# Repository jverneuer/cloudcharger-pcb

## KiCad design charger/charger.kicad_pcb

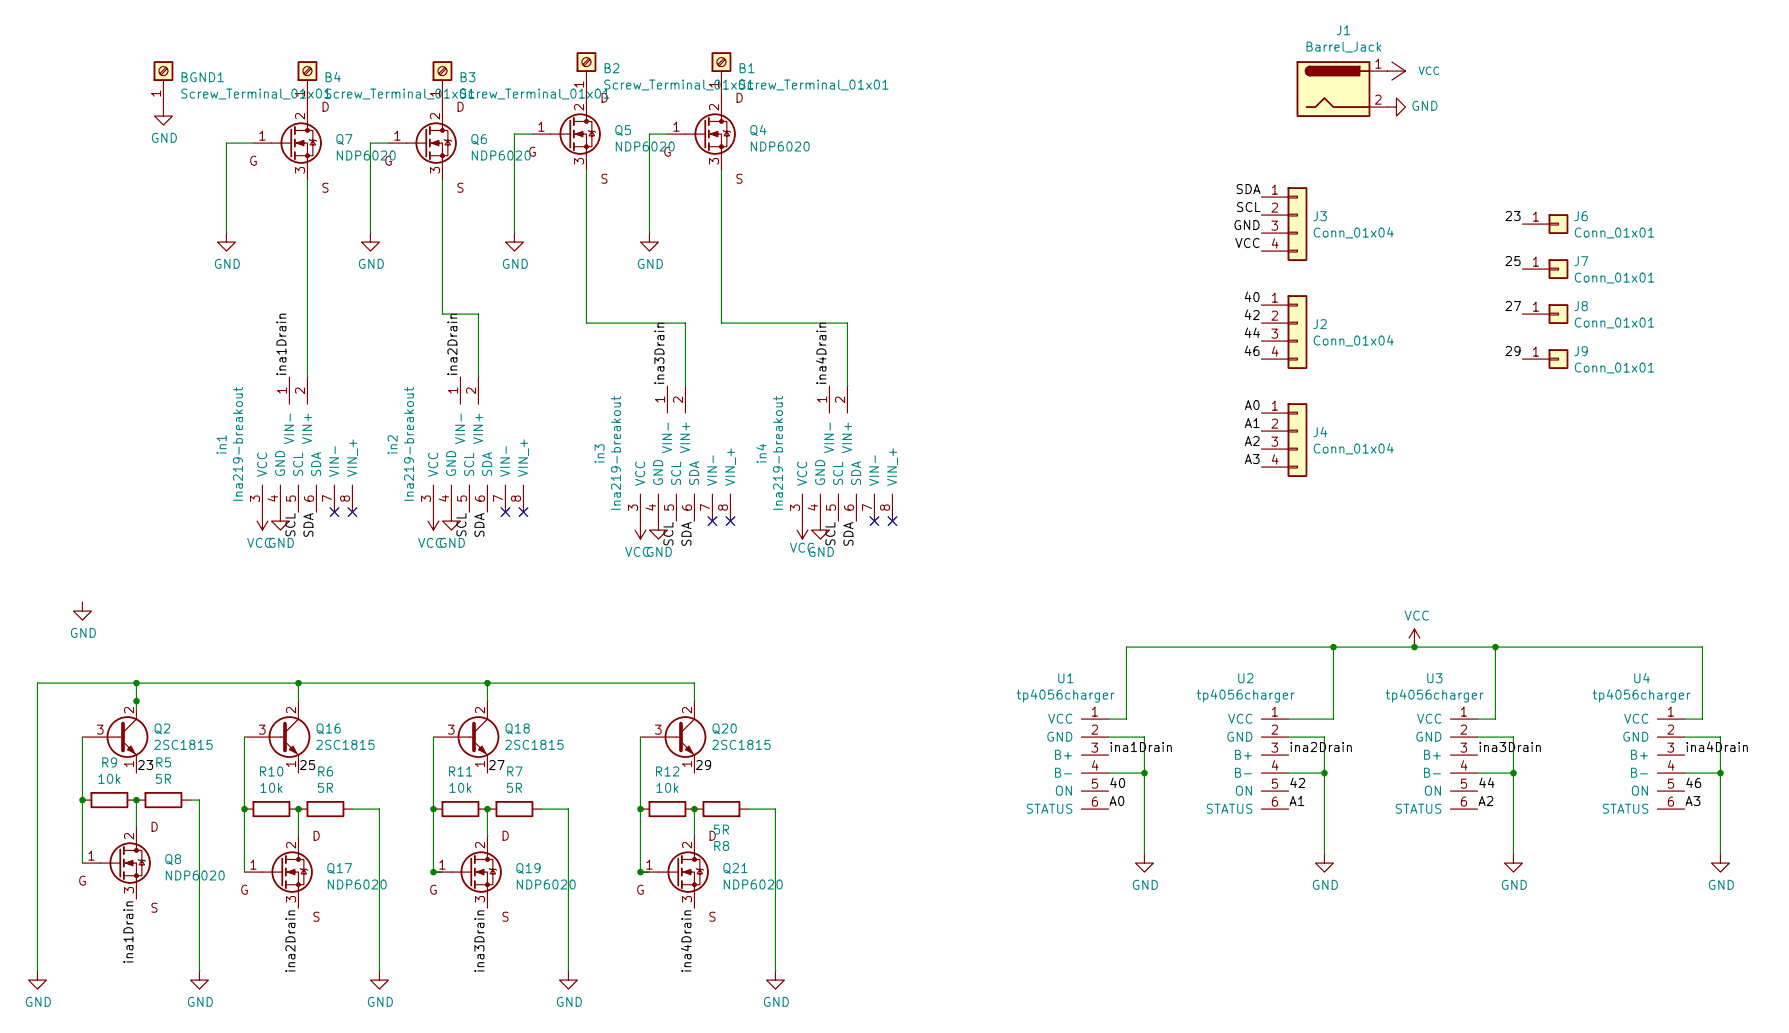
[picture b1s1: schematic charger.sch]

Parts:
B1, B2, B3, B4: Screw_Terminal_01x01; MountingHole_2.2mm_M2_DIN965_Pad
BGND1: Screw_Terminal_01x01; MountingHole_2.2mm_M2_DIN965_Pad
J1: Barrel_Jack; PinSocket_1x02_P2.54mm_Vertical
J2, J3, J4: Conn_01x04; PinHeader_1x04_P2.54mm_Vertical
J6, J7, J8, J9: Conn_01x01; PinHeader_1x01_P2.54mm_Vertical
Q2, Q16, Q18, Q20: 2SC1815; TO-92_Inline
Q4, Q5, Q6, Q7, Q8, Q17, Q19, Q21: NDP6020; TO-220-3_Vertical
R5, R6, R7, R8: 5R; R_Axial_DIN0204_L3.6mm_D1.6mm_P5.08mm_Vertical
R9, R10, R11, R12: 10k; R_Axial_DIN0204_L3.6mm_D1.6mm_P5.08mm_Vertical
U1, U2, U3, U4: tp4056charger; tp4056-breakout
in1, in2, in3, in4: Ina219-breakout; ina219_footprint

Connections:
/23: J6.1, Q2.1 (E)
/25: J7.1, Q16.1 (E)
/27: J8.1, Q18.1 (E)
/29: J9.1, Q20.1 (E)
/40: J2.1, U1.5 (ON)
/42: J2.2, U2.5 (ON)
/44: J2.3, U3.5 (ON)
/46: J2.4, U4.5 (ON)
/A0: J4.1, U1.6 (STATUS)
/A1: J4.2, U2.6 (STATUS)
/A2: J4.3, U3.6 (STATUS)
/A3: J4.4, U4.6 (STATUS)
/SCL: J3.2, in1.5 (SCL), in2.5 (SCL), in3.5 (SCL), in4.5 (SCL)
/SDA: J3.1, in1.6 (SDA), in2.6 (SDA), in3.6 (SDA), in4.6 (SDA)
/ina1Drain: Q8.3 (S), U1.3 (B+), in1.1 (VIN-)
/ina2Drain: Q17.3 (S), U2.3 (B+), in2.1 (VIN-)
/ina3Drain: Q19.3 (S), U3.3 (B+), in3.1 (VIN-)
/ina4Drain: Q21.3 (S), U4.3 (B+), in4.1 (VIN-)
GND: BGND1.1, J1.2, J3.3, Q2.2 (C), Q4.1 (G), Q5.1 (G), Q6.1 (G), Q7.1 (G), Q16.2 (C), Q18.2 (C), Q20.2 (C), R5.1, R6.1, R7.1, R8.2, U1.2 (GND), U1.4 (B-), U2.2 (GND), U2.4 (B-), U3.2 (GND), U3.4 (B-), U4.2 (GND), U4.4 (B-), in1.4 (GND), in2.4 (GND), in3.4 (GND), in4.4 (GND)
unnamed: B1.1, Q4.2 (D)
unnamed: B2.1, Q5.2 (D)
unnamed: B3.1, Q6.2 (D)
unnamed: B4.1, Q7.2 (D)
unnamed: Q2.3 (B), Q8.1 (G), R9.2
unnamed: Q4.3 (S), in4.2 (VIN+)
unnamed: Q5.3 (S), in3.2 (VIN+)
unnamed: Q6.3 (S), in2.2 (VIN+)
unnamed: Q7.3 (S), in1.2 (VIN+)
unnamed: Q8.2 (D), R5.2, R9.1
unnamed: Q16.3 (B), Q17.1 (G), R10.2
unnamed: Q17.2 (D), R6.2, R10.1
unnamed: Q18.3 (B), Q19.1 (G), R11.2
unnamed: Q19.2 (D), R7.2, R11.1
unnamed: Q20.3 (B), Q21.1 (G), R12.2
unnamed: Q21.2 (D), R8.1, R12.1
VCC: J1.1, J3.4, U1.1 (VCC), U2.1 (VCC), U3.1 (VCC), U4.1 (VCC), in1.3 (VCC), in2.3 (VCC), in3.3 (VCC), in4.3 (VCC)

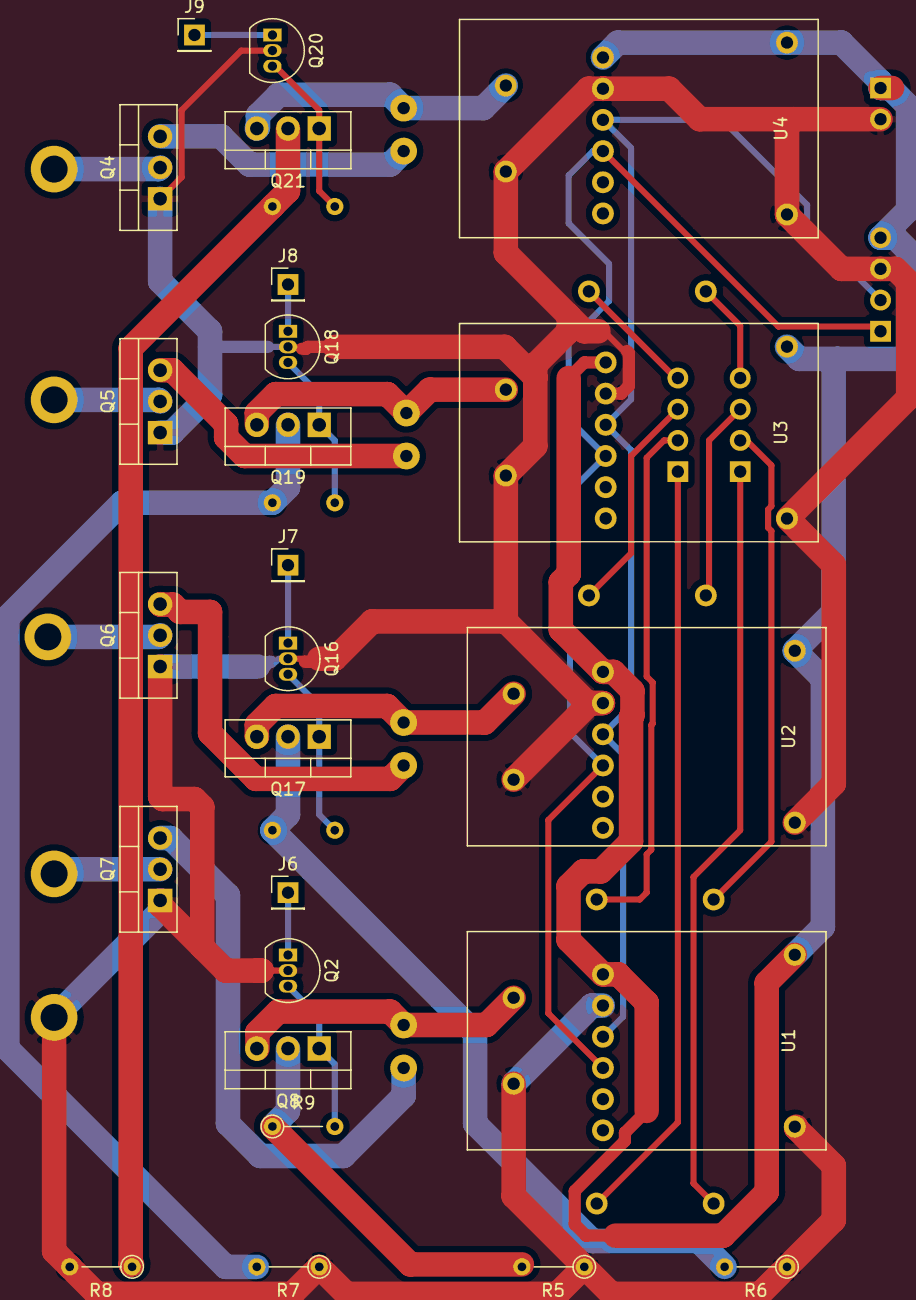
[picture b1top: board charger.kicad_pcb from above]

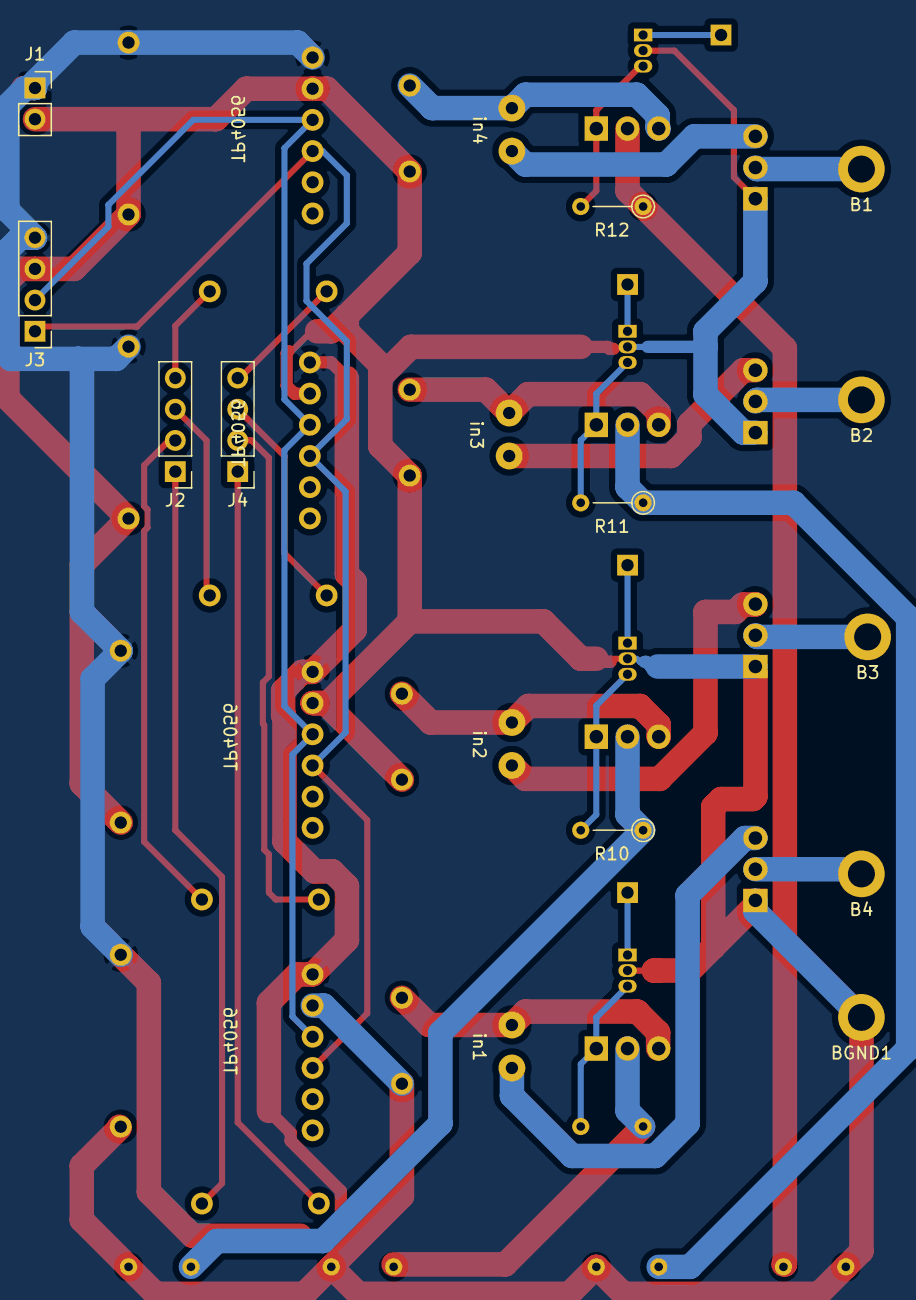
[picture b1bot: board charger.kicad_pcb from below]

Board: 2 copper layers, 41 parts (16 on the bottom side), 36 nets.

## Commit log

2021-06-06 adding 2 layer layout, circuit design for 1 and 2 layer
